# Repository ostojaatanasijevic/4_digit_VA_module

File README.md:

# 4_digit_VA_module
High accuracy module for voltage and current monitoring

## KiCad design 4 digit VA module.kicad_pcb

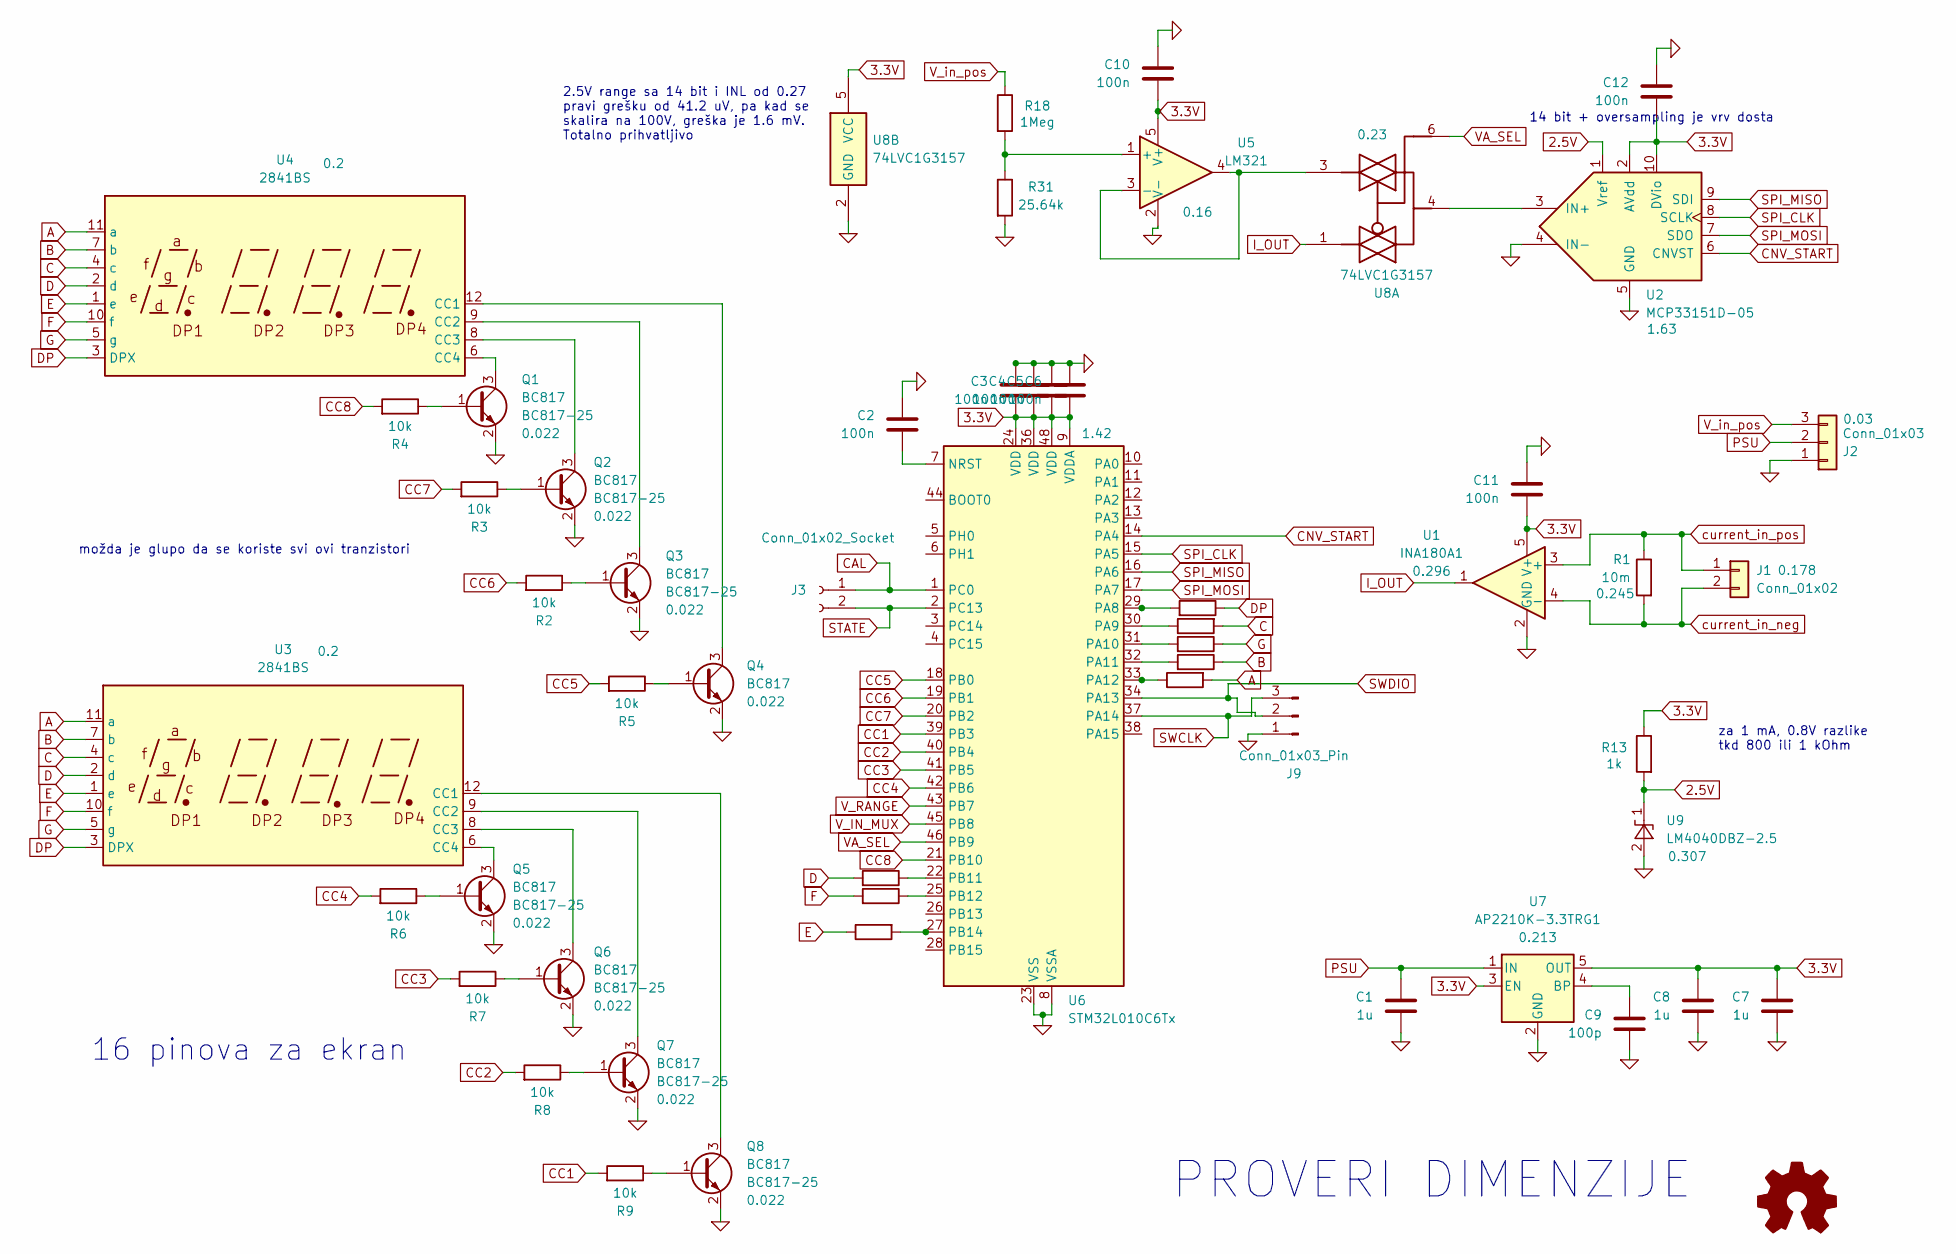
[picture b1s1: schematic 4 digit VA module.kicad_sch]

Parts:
C1, C7, C8: 1u; C_0603_1608Metric_Pad1.08x0.95mm_HandSolder
C2, C3, C4, C5, C6, C10, C11, C12: 100n; C_0603_1608Metric_Pad1.08x0.95mm_HandSolder
C9: 100p; C_0603_1608Metric_Pad1.08x0.95mm_HandSolder
J1: Conn_01x02; TerminalBlock_Altech_AK300-2_P5.00mm
J2: Conn_01x03; JST_EH_B3B-EH-A_1x03_P2.50mm_Vertical
J3: Conn_01x02_Socket; PinHeader_1x02_P2.54mm_Vertical
J9: Conn_01x03_Pin; PinHeader_1x03_P2.54mm_Vertical
Q1, Q2, Q3, Q4, Q5, Q6, Q7, Q8: BC817; SOT-23
R1: 10m; R_2512_6332Metric_Pad1.40x3.35mm_HandSolder
R2, R3, R4, R5, R6, R7, R8, R9: 10k; R_0603_1608Metric_Pad0.98x0.95mm_HandSolder
R13: 1k; R_0603_1608Metric_Pad0.98x0.95mm_HandSolder
R18: 1Meg; R_0603_1608Metric_Pad0.98x0.95mm_HandSolder
R31: 25.64k; R_0603_1608Metric_Pad0.98x0.95mm_HandSolder
R32, R33, R34, R35, R36, R37, R38, R39: 220; R_0603_1608Metric_Pad0.98x0.95mm_HandSolder
U1: INA180A1; SOT-23-5
U2: MCP33151D-05; MSOP-10_3x3mm_P0.5mm
U3, U4: 2841BS; 2841
U5: LM321; SOT-23-5
U6: STM32L010C6Tx; LQFP-48_7x7mm_P0.5mm
U7: AP2210K-3.3TRG1; SOT-23-5
U8: 74LVC1G3157; SOT-363_SC-70-6_Handsoldering
U9: LM4040DBZ-2.5; SOT-23

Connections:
0: C1.2, C2.1, C3.1, C4.1, C5.1, C6.1, C7.2, C8.2, C9.2, C10.1, C11.1, C12.1, J2.1, J9.1, Q1.2 (E), Q2.2 (E), Q3.2 (E), Q4.2 (E), Q5.2 (E), Q6.2 (E), Q7.2 (E), Q8.2 (E), R31.2, U1.2 (GND), U2.4 (IN-), U2.5 (GND), U5.2 (V-), U6.8 (VSSA), U6.23 (VSS), U6.35 (VSS), U6.47 (VSS), U7.2 (GND), U8.2 (GND), U9.2 (A)
2.5V: R13.2, U2.1 (Vref), U9.1 (K)
3.3V: C3.2, C4.2, C5.2, C6.2, C7.1, C8.1, C10.2, C11.2, C12.2, R13.1, U1.5 (V+), U2.2 (AVdd), U2.10 (DVio), U5.5 (V+), U6.9 (VDDA), U6.24 (VDD), U6.36 (VDD), U6.48 (VDD), U7.3 (EN), U7.5 (OUT), U8.5 (VCC)
A: R35.2, U3.11 (a), U4.11 (a)
B: R38.1, U3.7 (b), U4.7 (b)
C: R36.2, U3.4 (c), U4.4 (c)
CAL: J3.1, U6.1 (PC0)
CC1: R9.2, U6.39 (PB3)
CC2: R8.2, U6.40 (PB4)
CC3: R7.2, U6.41 (PB5)
CC4: R6.2, U6.42 (PB6)
CC5: R5.2, U6.18 (PB0)
CC6: R2.2, U6.19 (PB1)
CC7: R3.2, U6.20 (PB2)
CC8: R4.2, U6.21 (PB10)
CNV_START: U2.6 (CNVST), U6.14 (PA4)
D: R33.2, U3.2 (d), U4.2 (d)
DP: R39.1, U3.3 (DPX), U4.3 (DPX)
E: R32.1, U3.1 (e), U4.1 (e)
F: R34.2, U3.10 (f), U4.10 (f)
G: R37.1, U3.5 (g), U4.5 (g)
I_OUT: U1.1, U8.1
unnamed: Q1.1 (B), R4.1
unnamed: Q1.3 (C), U4.6 (CC4)
unnamed: Q2.1 (B), R3.1
unnamed: Q2.3 (C), U4.8 (CC3)
unnamed: Q3.1 (B), R2.1
unnamed: Q3.3 (C), U4.9 (CC2)
unnamed: Q4.1 (B), R5.1
unnamed: Q4.3 (C), U4.12 (CC1)
unnamed: Q5.1 (B), R6.1
unnamed: Q5.3 (C), U3.6 (CC4)
unnamed: Q6.1 (B), R7.1
unnamed: Q6.3 (C), U3.8 (CC3)
unnamed: Q7.1 (B), R8.1
unnamed: Q7.3 (C), U3.9 (CC2)
unnamed: Q8.1 (B), R9.1
unnamed: Q8.3 (C), U3.12 (CC1)
unnamed: U2.3 (IN+), U8.4
unnamed: R18.2, R31.1, U5.1 (+)
unnamed: U5.3 (-), U5.4, U8.3
unnamed: C2.2, U6.7 (NRST)
unnamed: R39.2, U6.29 (PA8)
unnamed: R36.1, U6.30 (PA9)
unnamed: R37.2, U6.31 (PA10)
unnamed: R38.2, U6.32 (PA11)
unnamed: R35.1, U6.33 (PA12)
unnamed: R33.1, U6.22 (PB11)
unnamed: R34.1, U6.25 (PB12)
unnamed: R32.2, U6.27 (PB14)
unnamed: C9.1, U7.4 (BP)
PSU: C1.1, J2.2, U7.1 (IN)
SPI_CLK: U2.8 (SCLK), U6.15 (PA5)
SPI_MISO: U2.9 (SDI), U6.16 (PA6)
SPI_MOSI: U2.7 (SDO), U6.17 (PA7)
STATE: J3.2, U6.2 (PC13)
SWCLK: J9.3, U6.37 (PA14)
SWDIO: J9.2, U6.34 (PA13)
VA_SEL: U6.46 (PB9), U8.6
V_IN_MUX: U6.45 (PB8)
V_RANGE: U6.43 (PB7)
V_in_pos: J2.3, R18.1
current_in_neg: J1.2, R1.2, U1.4 (-)
current_in_pos: J1.1, R1.1, U1.3 (+)

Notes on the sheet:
PROVERI DIMENZIJE
možda je glupo da se koriste svi ovi tranzistori
2.5V range sa 14 bit i INL od 0.27 pravi grešku od 41.2 uV, pa kad se skalira na 100V, greška je 1.6 mV. Totalno prihvatljivo
za 1 mA, 0.8V razlike tkd 800 ili 1 kOhm
14 bit + oversampling je vrv dosta
16 pinova za ekran

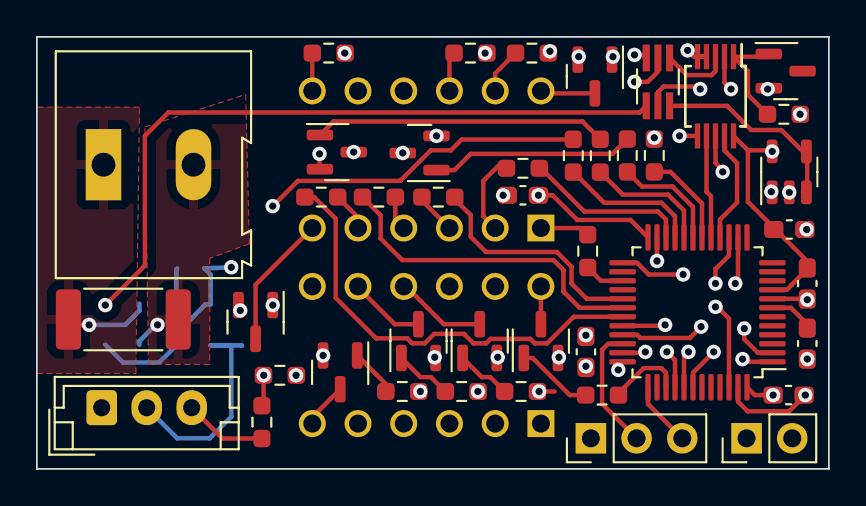
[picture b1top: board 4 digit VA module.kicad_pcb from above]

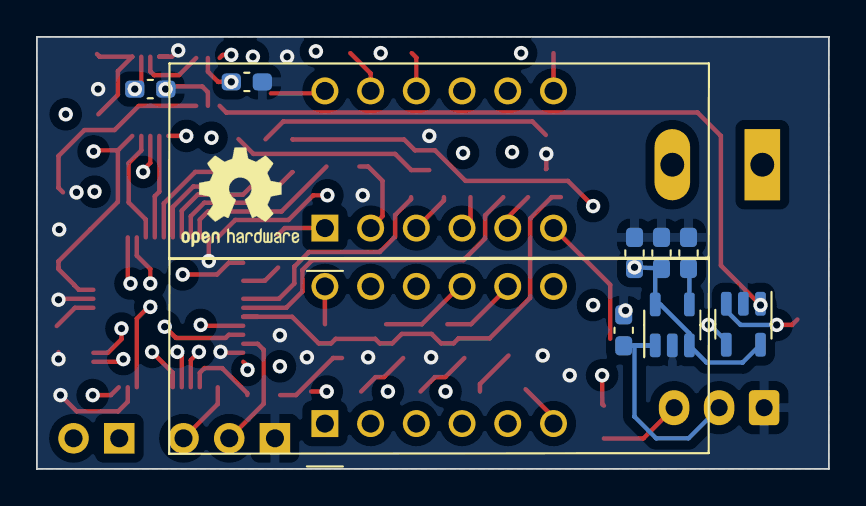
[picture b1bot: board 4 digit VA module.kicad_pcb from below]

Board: 4 copper layers, 44.0 x 24.0 mm, 53 parts (10 on the bottom side), 62 nets.

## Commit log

2023-10-30 Schematic najvrv gotov, cena oko 70E
2023-11-03 Samo 7 seg je kinezijum
    12 bit je malo cheapout, ukupna cena 5.8 EUR.
2023-11-04 Work in progress
2023-11-04 BOM za ne kinezijum je 5.3, totalno prihvatljivo.
2023-11-06 Izgleda kao da je PCB gotov, treba proveriti dimenziju.
